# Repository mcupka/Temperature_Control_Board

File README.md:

Temperature Control Board

This is a control board for a toaster oven reflow project. It will use the following major parts:

- ESP32 module for processing (wifi / bluetooth maybe?)
- MAX31855 to interface with the thermocouple
- SD Card interface
- I2C interface for OLED display
- UART for debug / programming (microusb?)
- Extra IOs and interfaces available for future uses of this board

Release V1.0 Images:

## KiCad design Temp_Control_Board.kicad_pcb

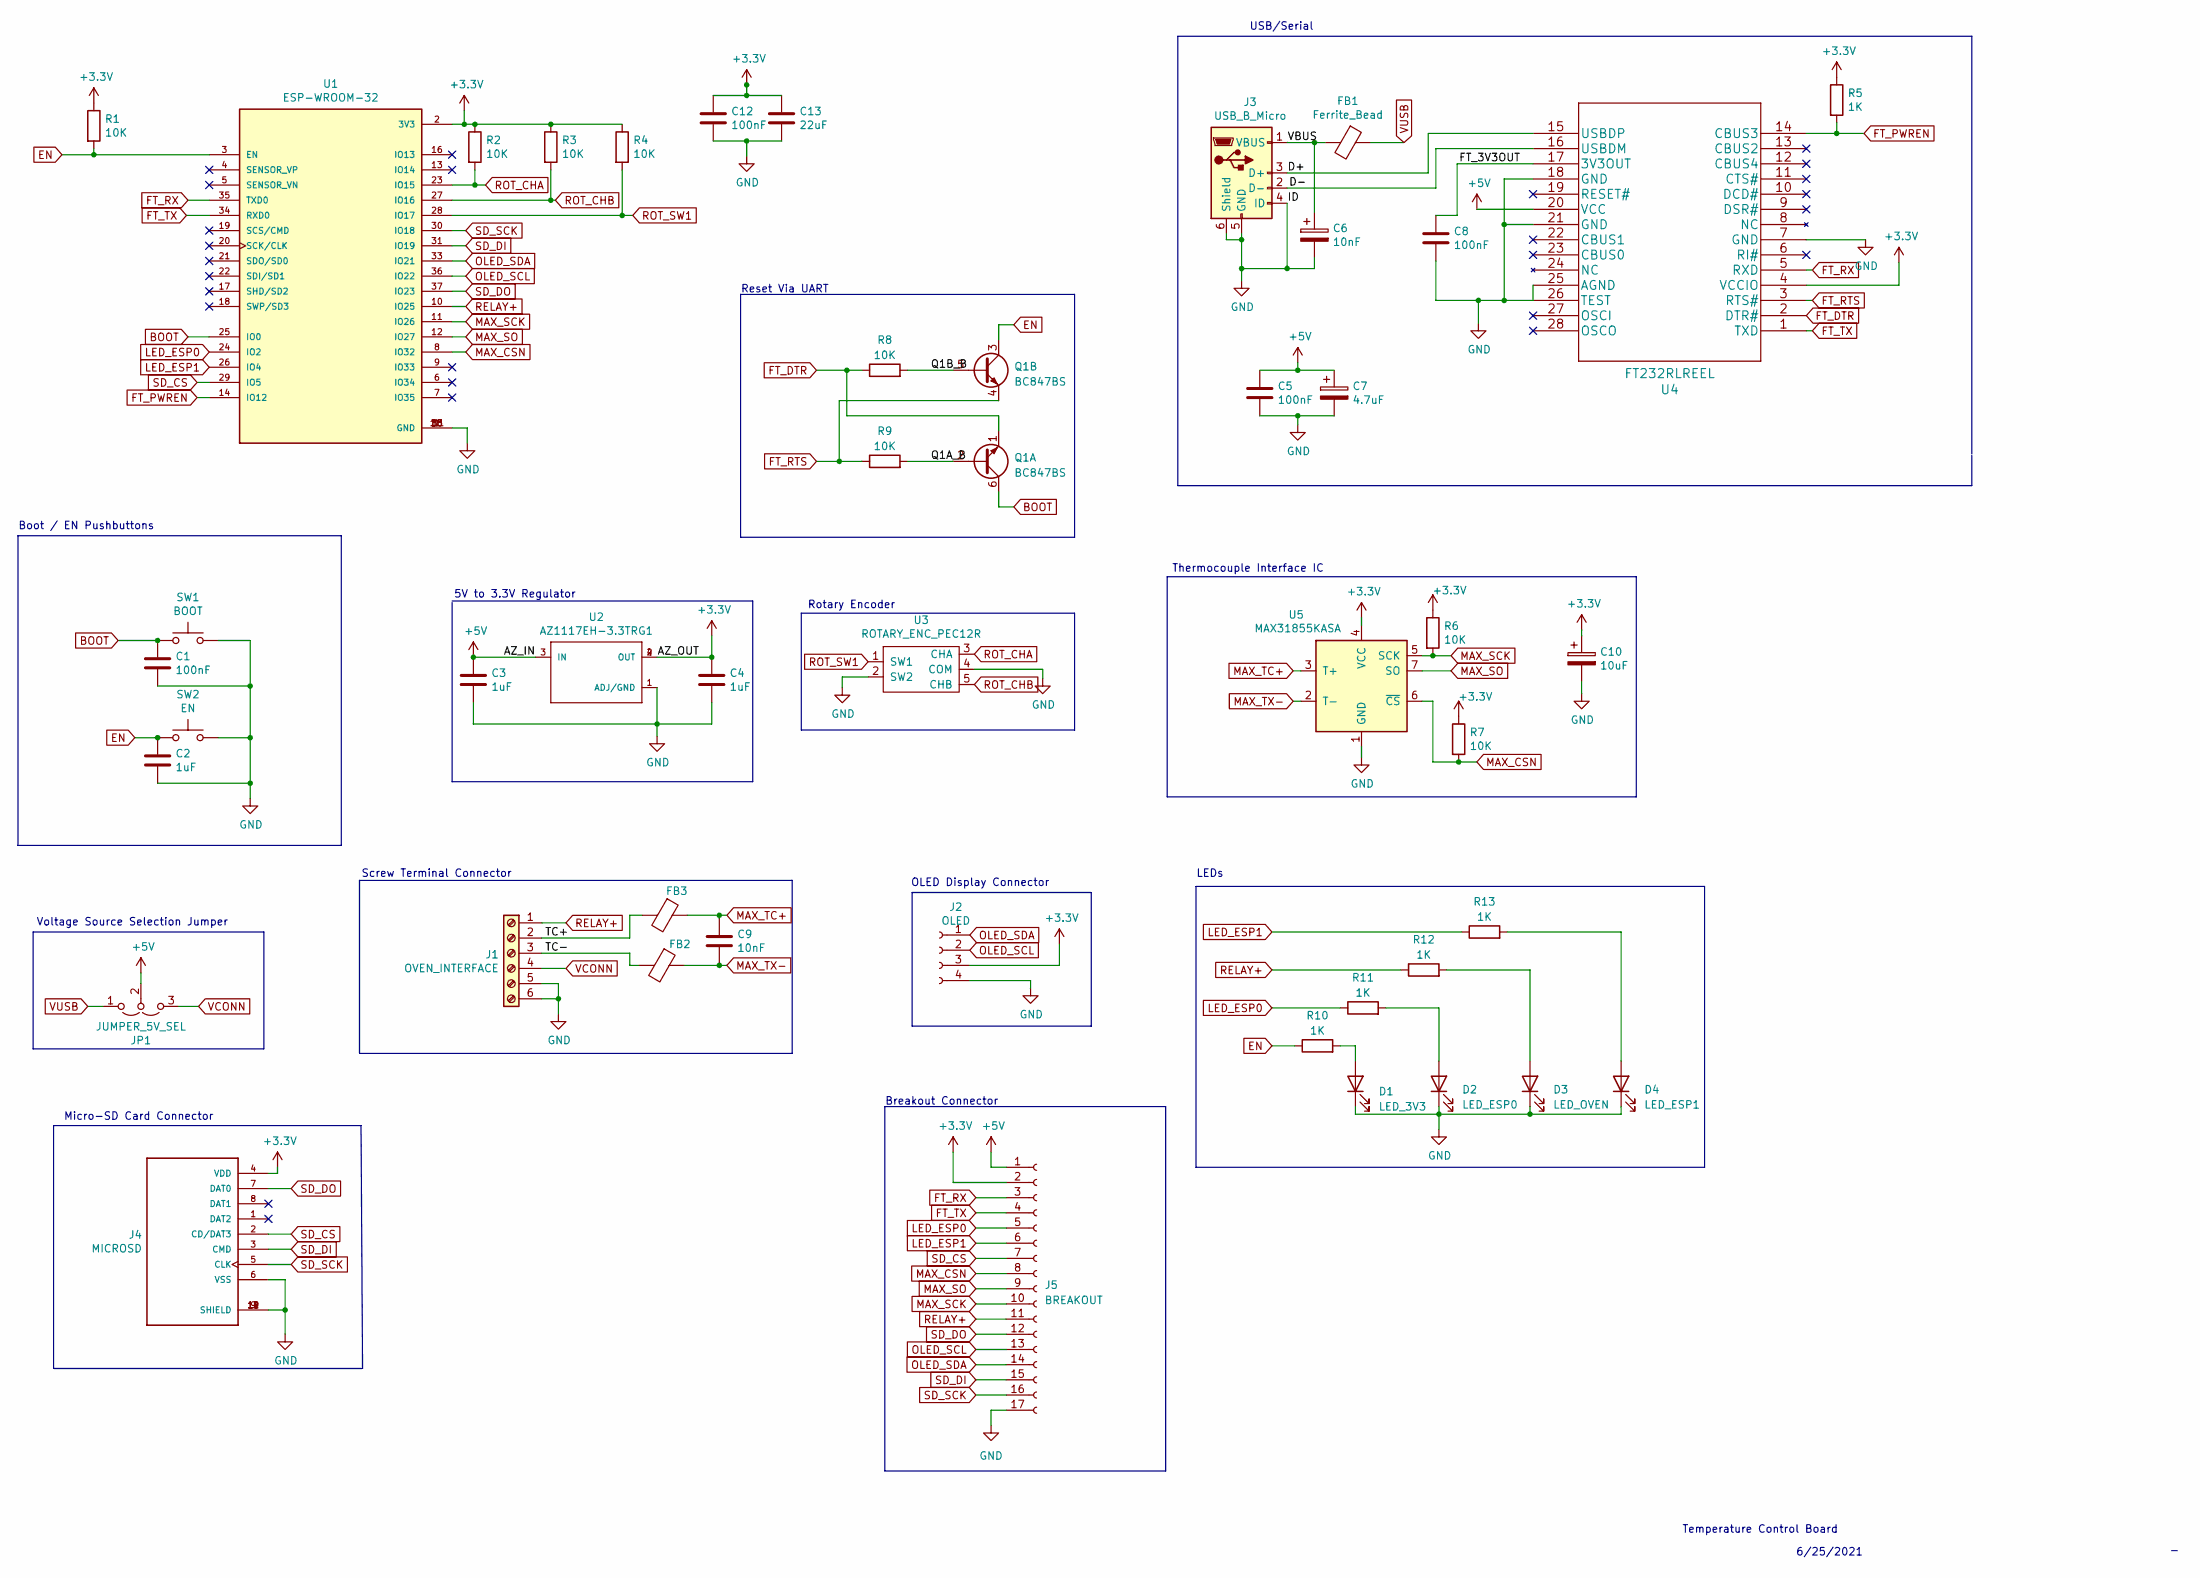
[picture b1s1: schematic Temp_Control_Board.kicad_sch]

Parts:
C1, C5, C8, C12: 100nF; C_0805_2012Metric_Pad1.18x1.45mm_HandSolder
C2, C3, C4: 1uF; C_0805_2012Metric_Pad1.18x1.45mm_HandSolder
C6, C9: 10nF; C_0805_2012Metric_Pad1.18x1.45mm_HandSolder
C7: 4.7uF; C_0805_2012Metric_Pad1.18x1.45mm_HandSolder
C10: 10uF; C_0805_2012Metric_Pad1.18x1.45mm_HandSolder
C13: 22uF; C_0805_2012Metric_Pad1.18x1.45mm_HandSolder
D1: LED_3V3; LED_0805_2012Metric_Pad1.15x1.40mm_HandSolder
D2: LED_ESP0; LED_0805_2012Metric_Pad1.15x1.40mm_HandSolder
D3: LED_OVEN; LED_0805_2012Metric_Pad1.15x1.40mm_HandSolder
D4: LED_ESP1; LED_0805_2012Metric_Pad1.15x1.40mm_HandSolder
FB1, FB2, FB3: Ferrite_Bead; R_0805_2012Metric_Pad1.20x1.40mm_HandSolder
J1: OVEN_INTERFACE; TerminalBlock_bornier-6_P5.08mm
J2: OLED; PinHeader_1x04_P2.54mm_Vertical
J3: USB_B_Micro; GCT_USB3076-XX-X_REVC
J4: MICROSD; GCT_MEM2067-02-180-00-A_REVB
J5: BREAKOUT; PinHeader_1x17_P2.54mm_Vertical
JP1: JUMPER_5V_SEL; SolderJumper-3_P1.3mm_Open_Pad1.0x1.5mm
Q1: BC847BS; SOT-363_SC-70-6
R1, R2, R3, R4, R6, R7, R8, R9: 10K; R_0805_2012Metric_Pad1.20x1.40mm_HandSolder
R5, R10, R11, R12, R13: 1K; R_0805_2012Metric_Pad1.20x1.40mm_HandSolder
SW1: BOOT; PTS645SK43SMTR92LF-CONNECTED
SW2: EN; PTS645SK43SMTR92LF-CONNECTED
U1: ESP-WROOM-32; MODULE_ESP-WROOM-32
U2: AZ1117EH-3.3TRG1; SOT230P700X180-4N
U3: ROTARY_ENC_PEC12R
U4: FT232RLREEL
U5: MAX31855KASA; SOIC-8_3.9x4.9mm_P1.27mm

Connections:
+3V3: C4.1, C10.1, C12.1, C13.1, J2.3, J4.4 (VDD), J5.2, R1.1, R2.1, R3.1, R4.1, R5.1, R6.1, R7.1, U1.2 (3V3), U2.2 (OUT), U2.4 (OUT), U4.4 (VCCIO), U5.4 (VCC)
+5V: C3.1, C5.1, C7.1, J5.1, JP1.2 (C), U2.3 (IN), U4.20 (VCC)
/D+: J3.3 (D+), U4.15 (USBDP)
/D-: J3.2 (D-), U4.16 (USBDM)
/FT_3V3OUT: C8.1, U4.17 (3V3OUT)
/Q1A_B: Q1.2 (B1), R9.2
/Q1B_B: Q1.5 (B2), R8.2
/TC+: FB3.2, J1.2
/TC-: FB2.2, J1.3
/VBUS: C6.1, FB1.2, J3.1 (VBUS)
BOOT: C1.1, Q1.6 (C1), SW1.1, U1.25 (IO0)
EN: C2.1, Q1.3 (C2), R1.2, R10.1, SW2.1, U1.3 (EN)
FT_DTR: Q1.1 (E1), R8.1, U4.2 (DTR#)
FT_PWREN: R5.2, U1.14 (IO12), U4.14 (CBUS3)
FT_RTS: Q1.4 (E2), R9.1, U4.3 (RTS#)
FT_RX: J5.3, U1.35 (TXD0), U4.5 (RXD)
FT_TX: J5.4, U1.34 (RXD0), U4.1 (TXD)
GND: C1.2, C2.2, C3.2, C4.2, C5.2, C6.2, C7.2, C8.2, C10.2, C12.2, C13.2, D1.1 (K), D2.1 (K), D3.1 (K), D4.1 (K), J1.5, J1.6, J2.4, J3.4 (ID), J3.5 (GND), J3.6 (Shield), J4.6 (VSS), J4.9 (SHIELD), J4.10 (SHIELD), J4.11 (SHIELD), J4.12 (SHIELD), J5.17, SW1.2, SW2.2, U1.1 (GND), U1.1.1 (GND), U1.15 (GND), U1.38 (GND), U2.1 (ADJ/GND), U3.2 (SW2), U3.4 (COM), U4.7 (GND), U4.18 (GND), U4.21 (GND), U4.25 (AGND), U4.26 (TEST), U5.1 (GND)
LED_ESP0: J5.5, R11.1, U1.24 (IO2)
LED_ESP1: J5.6, R13.1, U1.26 (IO4)
MAX_CSN: J5.8, R7.2, U1.8 (IO32), U5.6 (~CS)
MAX_SCK: J5.10, R6.2, U1.11 (IO26), U5.5 (SCK)
MAX_SO: J5.9, U1.12 (IO27), U5.7 (SO)
MAX_TC+: C9.1, FB3.1, U5.3 (T+)
MAX_TX-: C9.2, FB2.1, U5.2 (T-)
unnamed: D1.2 (A), R10.2
unnamed: D2.2 (A), R11.2
unnamed: D3.2 (A), R12.2
unnamed: D4.2 (A), R13.2
OLED_SCL: J2.2, J5.13, U1.36 (IO22)
OLED_SDA: J2.1, J5.14, U1.33 (IO21)
RELAY+: J1.1, J5.11, R12.1, U1.10 (IO25)
ROT_CHA: R2.2, U1.23 (IO15), U3.3 (CHA)
ROT_CHB: R3.2, U1.27 (IO16), U3.5 (CHB)
ROT_SW1: R4.2, U1.28 (IO17), U3.1 (SW1)
SD_CS: J4.2 (CD/DAT3), J5.7, U1.29 (IO5)
SD_DI: J4.3 (CMD), J5.15, U1.31 (IO19)
SD_DO: J4.7 (DAT0), J5.12, U1.37 (IO23)
SD_SCK: J4.5 (CLK), J5.16, U1.30 (IO18)
VCONN: J1.4, JP1.3 (B)
VUSB: FB1.1, JP1.1 (A)

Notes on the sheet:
Screw Terminal Connector
Thermocouple Interface IC
Reset Via UART
6/25/2021
Breakout Connector
Micro-SD Card Connector
OLED Display Connector
LEDs
Voltage Source Selection Jumper
USB/Serial
5V to 3.3V Regulator
Temperature Control Board
Boot / EN Pushbuttons
Rotary Encoder

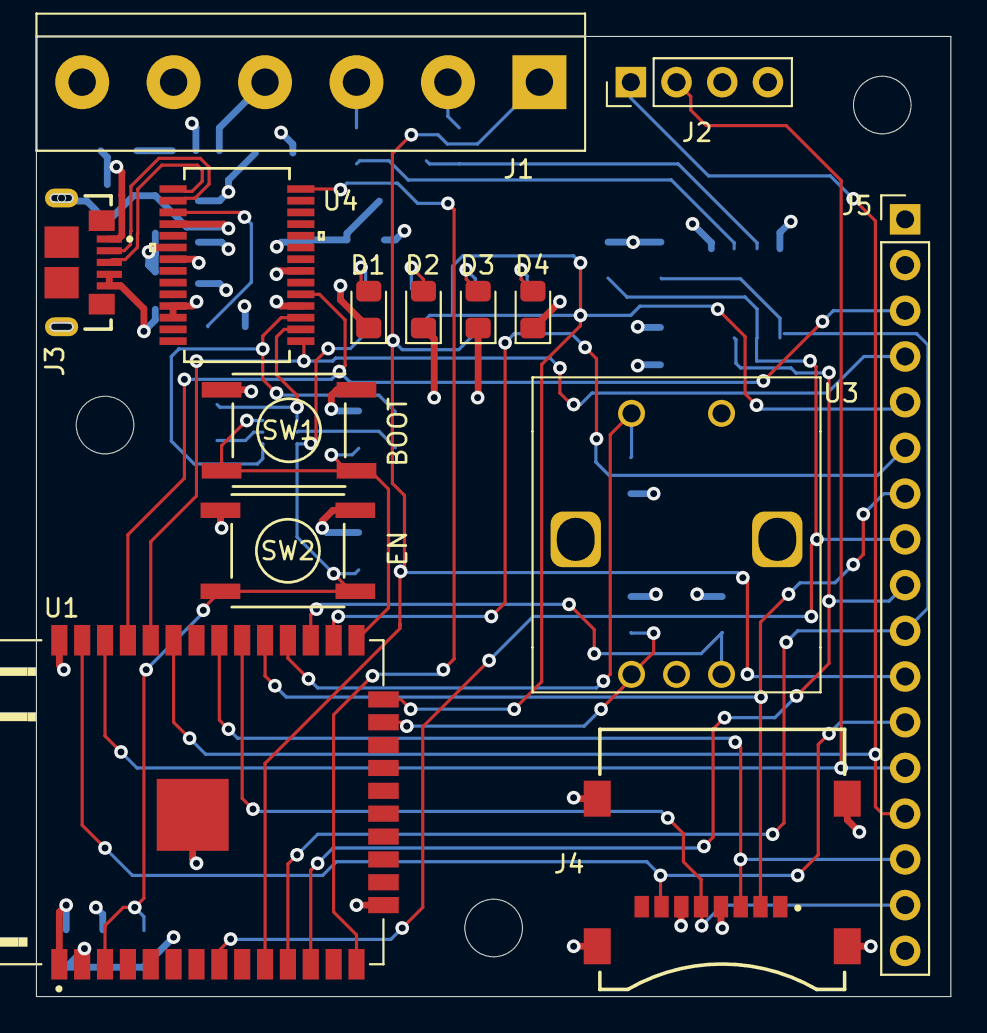
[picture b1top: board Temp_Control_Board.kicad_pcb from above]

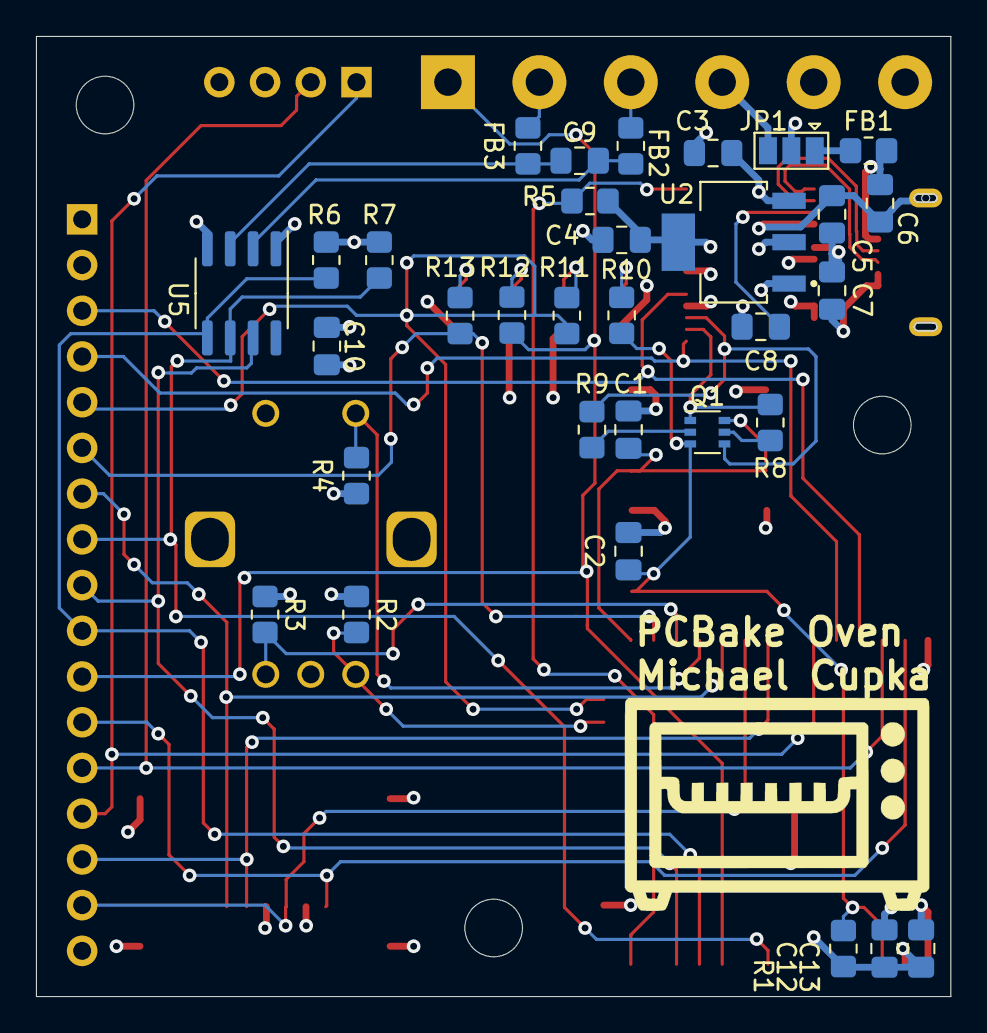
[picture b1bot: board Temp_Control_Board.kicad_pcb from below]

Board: 4 copper layers, 50.8 x 53.3 mm, 46 parts (32 on the bottom side), 41 nets.

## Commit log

2021-04-15 project: Initial commit sch: Initial commit pcb: Initial commit syms: Initial commit foots: Initial commit
2021-06-26 sch: First revision completed pcb: Footprints completed, first placement of components done. No routing.
2021-06-26 pro: set track widths
    pcb: routed power and ground
2021-07-06 ORD airport
2021-07-06 After airport. Routed, needs touching up.
2021-08-20 pcb: Finished Routing
    -Touched up some traces
    -Made silkscreen presentable
2021-08-20 Update README.md
    fixed image links
2021-08-27 git: added parts, gerbers, images, bom to git
2022-07-04 proj: Updated to KiCAD 6
    - removed old files with KiCAD 5 extensions, added new files.
    - added footprint and symbol library tables
    - ignored autosave, cache, and backup data
    - added .gitignore
2022-07-04 foots: Fixed tactile switch footprint and USB footprint
    - Tactile switch had wrong pins showing as connected internally
    - Changed through-hole pads for shield on USB connected to use actual oval pad instead of polygons
2022-07-04 pcb/shc: Fixed tactile switch routing, tied USB shield to GND
2022-07-11 parts: added esp32 datasheet
2022-07-11 sw: added hardware test repo as submodule
2023-03-18 Fixed BOOT / EN SWs ref designators
    - Fixes #4
2023-03-18 Changed all .1uF cap values to 100nF for consistency
    - Fixes #5
2023-03-18 sch: changed SD card pis to use SPI3 (VSPI)
    - Moved FT232 RTS and CTS pins to floating for now. These
    should be tied into the reset-esp32-via-UART circuit
    anyway
2023-03-18 sch: increased C between EN and GND
    - Necessary to increase capacitance for reset to work correctly
2023-03-30 Began adding reset circuit to schematic
2023-03-30 update to KiCAD 7
2023-04-01 sch: Added reset via UART circuit
2023-04-01 sch: Added LEDs
    - Added LEDs for 3.3V, Oven relay enabled, and two
    general purpose LEDs connected to ESP32
2023-04-01 sch: added 2.54mm pitch breakout connector
    - Breaks out many signals connected to ESP32
    as well as 3.3V, 5V, and GND
    - Intended for testing or for alternate uses
    of this board
2023-04-01 pcb: began re-routing pcb following fixes
    - Switched to much smaller, 4-layer board
2023-04-07 pcb: components placed
    - sch: fixed FT_CTS -> FT_RTS on reset circuit
2023-04-07 pcb: began routing
    - Updated ESP32 part to new KiCAD version
2023-04-22 simple routing complete
    - Mostly North/South on front Copper, mostly East/West on Back
    Copper
2023-05-19 pcb: Finished routing

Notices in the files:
parts and their libraries:
Copyright 2016 Accelerated Designs. All rights reserved.
